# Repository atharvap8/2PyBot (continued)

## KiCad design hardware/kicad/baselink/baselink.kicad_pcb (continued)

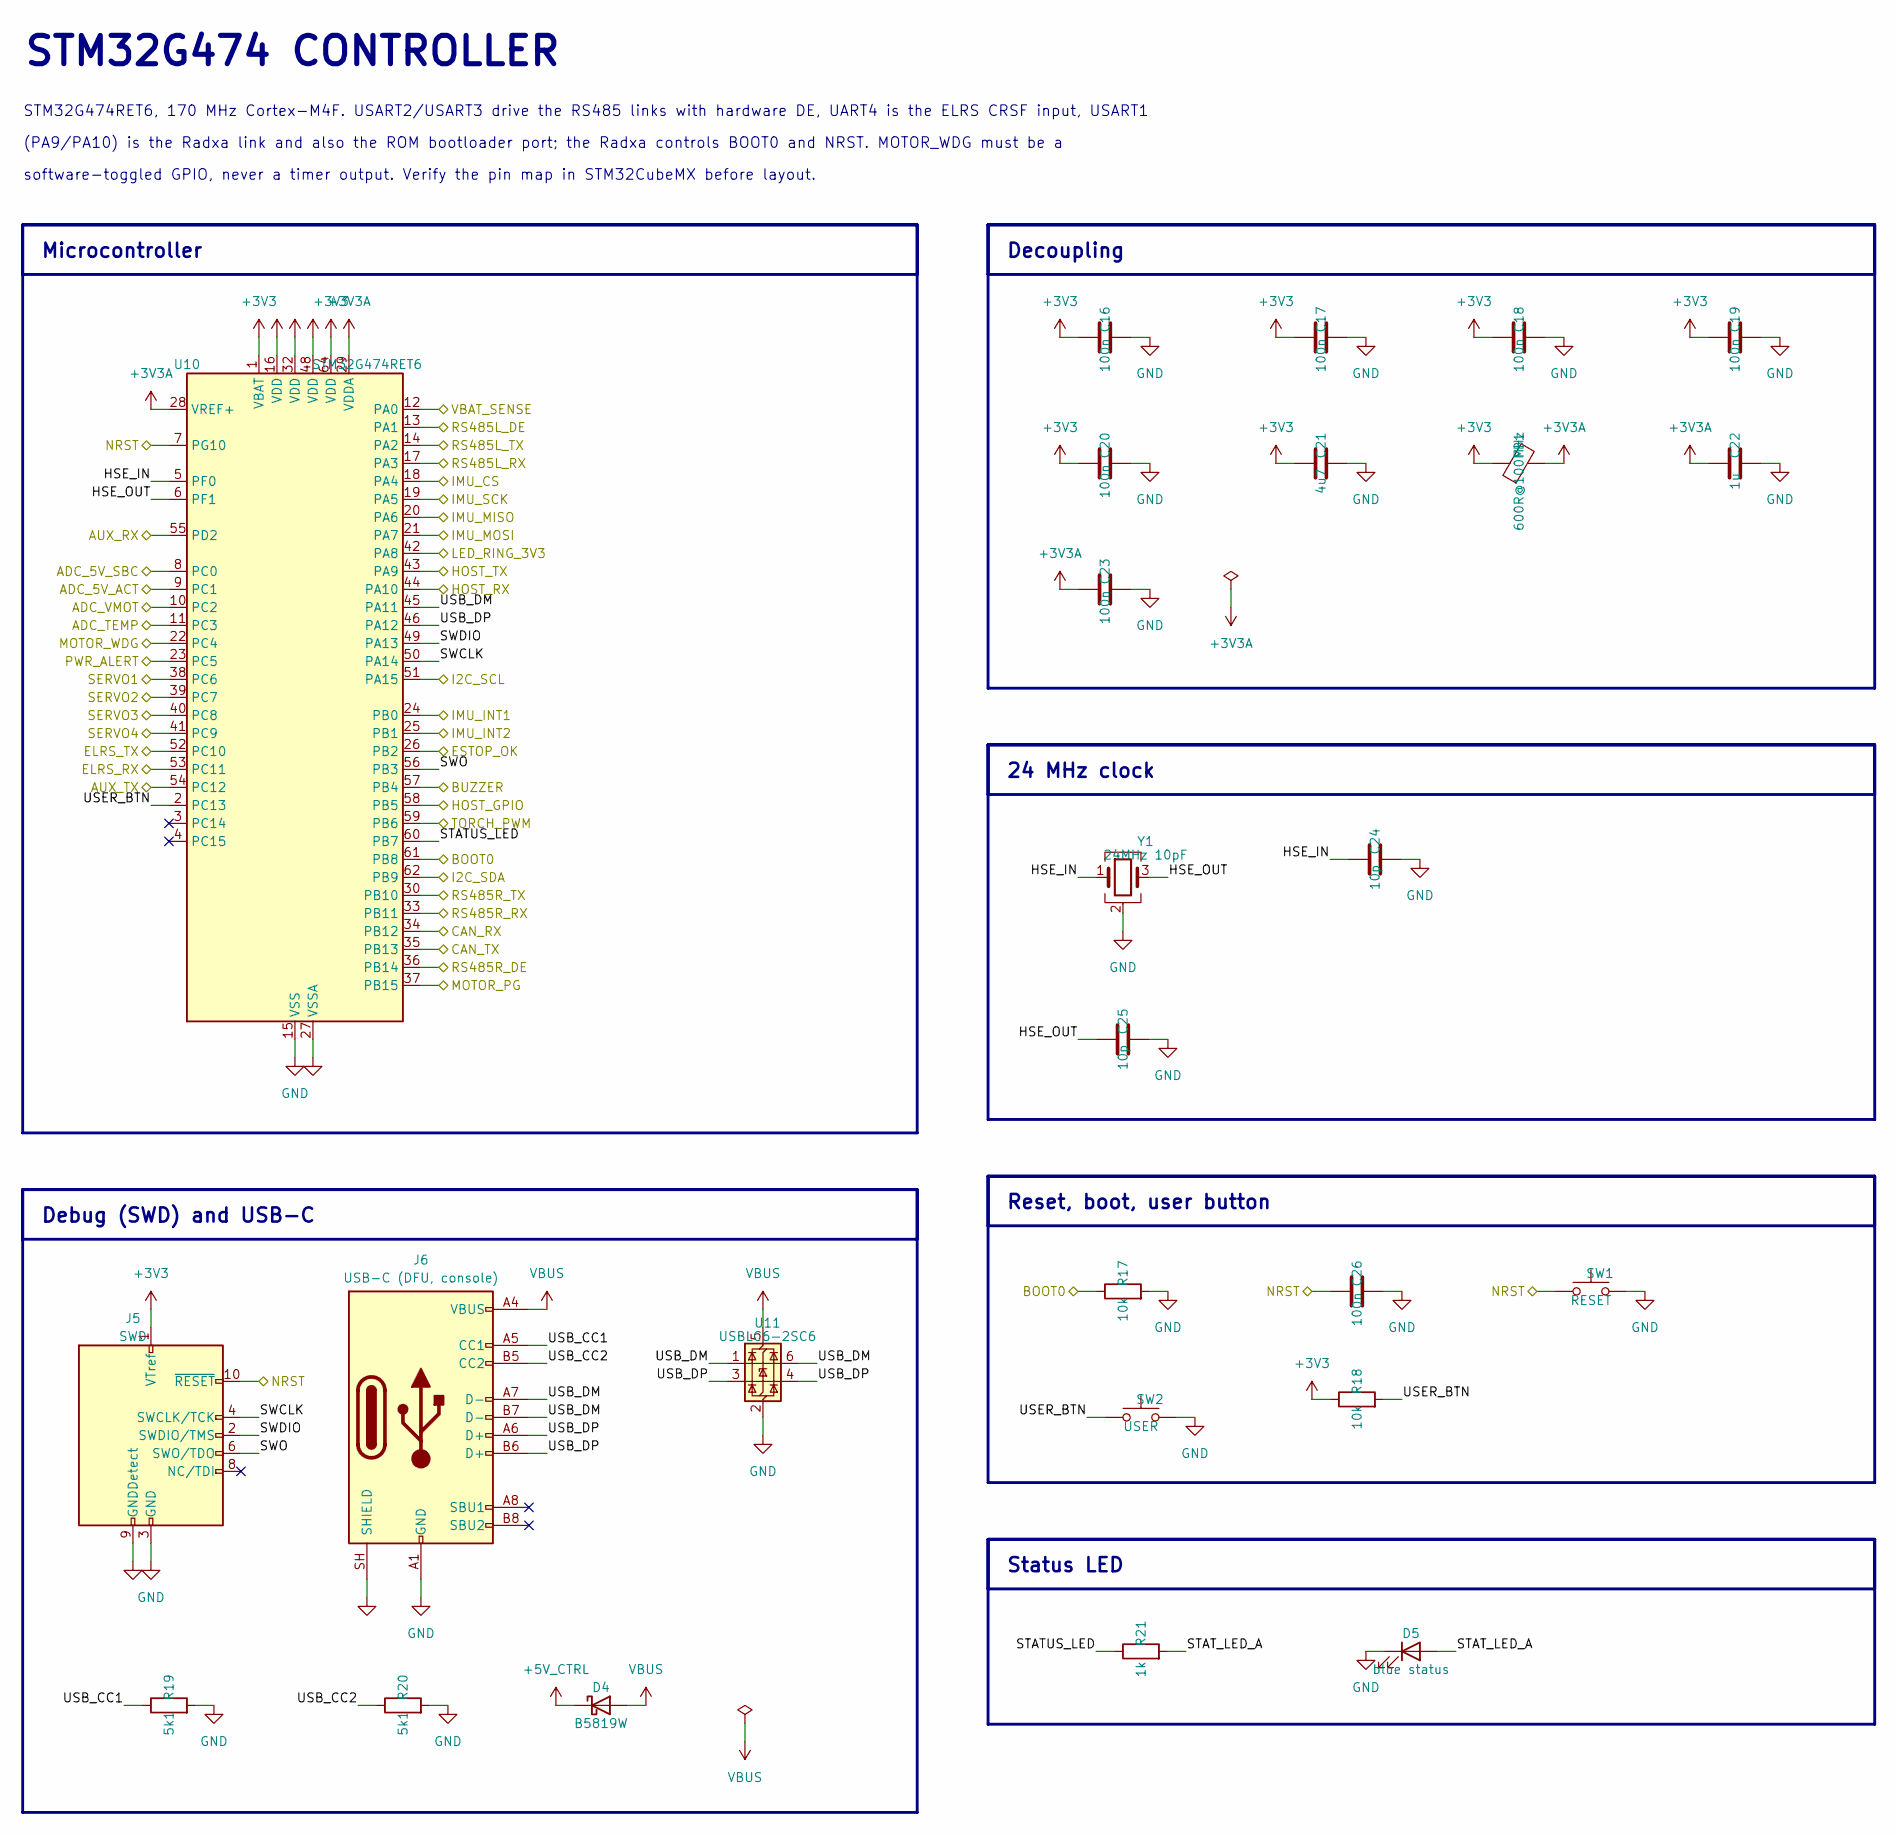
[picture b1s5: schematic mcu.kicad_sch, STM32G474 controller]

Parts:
C16, C17, C18, C19, C20, C23, C26: 100n; C_0603_1608Metric
C21: 4u7; C_0805_2012Metric
C22: 1u; C_0603_1608Metric
C24, C25: 10p; C_0603_1608Metric
D4: B5819W; D_SOD-123
D5: blue status; LED_0603_1608Metric
FB1: 600R@100MHz; L_0603_1608Metric
J5: SWD; PinHeader_2x05_P1.27mm_Vertical_SMD
J6: USB-C (DFU, console); USB_C_Receptacle_GCT_USB4105-xx-A_16P_TopMnt_Horizontal
R17, R18: 10k; R_0603_1608Metric
R19, R20: 5k1; R_0603_1608Metric
R21: 1k; R_0603_1608Metric
SW1: RESET; SW_SPST_TL3342
SW2: USER; SW_SPST_TL3342
U10: STM32G474RET6; LQFP-64_10x10mm_P0.5mm
U11: USBLC6-2SC6; SOT-23-6
Y1: 24MHz 10pF; Crystal_SMD_3225-4Pin_3.2x2.5mm

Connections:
+3V3: C16.1, C17.1, C18.1, C19.1, C20.1, C21.1, FB1.1, J5.1 (VTref), R18.1, U10.1 (VBAT), U10.16 (VDD), U10.32 (VDD), U10.48 (VDD), U10.64 (VDD); also elsewhere on the board
+3V3A: C22.1, C23.1, FB1.2, U10.28 (VREF+), U10.29 (VDDA)
+5V_CTRL: D4.1 (K); also elsewhere on the board
/ADC_5V_ACT: U10.9 (PC1); also elsewhere on the board
/ADC_5V_SBC: U10.8 (PC0); also elsewhere on the board
/ADC_TEMP: U10.11 (PC3); also elsewhere on the board
/ADC_VMOT: U10.10 (PC2); also elsewhere on the board
/AUX_RX: U10.55 (PD2); also elsewhere on the board
/AUX_TX: U10.54 (PC12); also elsewhere on the board
/BOOT0: R17.1, U10.61 (PB8); also elsewhere on the board
/BUZZER: U10.57 (PB4); also elsewhere on the board
/CAN_RX: U10.34 (PB12); also elsewhere on the board
/CAN_TX: U10.35 (PB13); also elsewhere on the board
/ELRS_RX: U10.53 (PC11); also elsewhere on the board
/ELRS_TX: U10.52 (PC10); also elsewhere on the board
/ESTOP_OK: U10.26 (PB2); also elsewhere on the board
/HOST_GPIO: U10.58 (PB5); also elsewhere on the board
/HOST_RX: U10.44 (PA10); also elsewhere on the board
/HOST_TX: U10.43 (PA9); also elsewhere on the board
/I2C_SCL: U10.51 (PA15); also elsewhere on the board
/I2C_SDA: U10.62 (PB9); also elsewhere on the board
/IMU_CS: U10.18 (PA4); also elsewhere on the board
/IMU_INT1: U10.24 (PB0); also elsewhere on the board
/IMU_INT2: U10.25 (PB1); also elsewhere on the board
/IMU_MISO: U10.20 (PA6); also elsewhere on the board
/IMU_MOSI: U10.21 (PA7); also elsewhere on the board
/IMU_SCK: U10.19 (PA5); also elsewhere on the board
/LED_RING_3V3: U10.42 (PA8); also elsewhere on the board
/MCU/HSE_IN: C24.1, U10.5 (PF0), Y1.1
/MCU/HSE_OUT: C25.1, U10.6 (PF1), Y1.3
/MCU/STATUS_LED: R21.1, U10.60 (PB7)
/MCU/STAT_LED_A: D5.2 (A), R21.2
/MCU/SWCLK: J5.4 (SWCLK/TCK), U10.50 (PA14)
/MCU/SWDIO: J5.2 (SWDIO/TMS), U10.49 (PA13)
/MCU/SWO: J5.6 (SWO/TDO), U10.56 (PB3)
/MCU/USB_CC1: J6.A5 (CC1), R19.1
/MCU/USB_CC2: J6.B5 (CC2), R20.1
/MCU/USB_DM: J6.A7 (D-), J6.B7 (D-), U10.45 (PA11), U11.1 (I/O1), U11.6 (I/O1)
/MCU/USB_DP: J6.A6 (D+), J6.B6 (D+), U10.46 (PA12), U11.3 (I/O2), U11.4 (I/O2)
/MCU/USER_BTN: R18.2, SW2.1, U10.2 (PC13)
/MOTOR_PG: U10.37 (PB15); also elsewhere on the board
/MOTOR_WDG: U10.22 (PC4); also elsewhere on the board
/NRST: C26.1, J5.10 (~RESET), SW1.1, U10.7 (PG10); also elsewhere on the board
/PWR_ALERT: U10.23 (PC5); also elsewhere on the board
/RS485L_DE: U10.13 (PA1); also elsewhere on the board
/RS485L_RX: U10.17 (PA3); also elsewhere on the board
/RS485L_TX: U10.14 (PA2); also elsewhere on the board
/RS485R_DE: U10.36 (PB14); also elsewhere on the board
/RS485R_RX: U10.33 (PB11); also elsewhere on the board
/RS485R_TX: U10.30 (PB10); also elsewhere on the board
/SERVO1: U10.38 (PC6); also elsewhere on the board
/SERVO2: U10.39 (PC7); also elsewhere on the board
/SERVO3: U10.40 (PC8); also elsewhere on the board
/SERVO4: U10.41 (PC9); also elsewhere on the board
/TORCH_PWM: U10.59 (PB6); also elsewhere on the board
/VBAT_SENSE: U10.12 (PA0); also elsewhere on the board
GND: C16.2, C17.2, C18.2, C19.2, C20.2, C21.2, C22.2, C23.2, C24.2, C25.2, C26.2, D5.1 (K), J5.3 (GND), J5.5 (GND), J5.9 (GNDDetect), J6.A1 (GND), J6.A12 (GND), J6.B1 (GND), J6.B12 (GND), J6.SH (SHIELD), R17.2, R19.2, R20.2, SW1.2, SW2.2, U10.15 (VSS), U10.27 (VSSA), U10.31 (VSS), U10.47 (VSS), U10.63 (VSS), U11.2 (GND), Y1.2 (G), Y1.4 (G); also elsewhere on the board
VBUS: D4.2 (A), J6.A4 (VBUS), J6.A9 (VBUS), J6.B4 (VBUS), J6.B9 (VBUS), U11.5 (VBUS)

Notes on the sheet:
STM32G474 CONTROLLER
STM32G474RET6, 170 MHz Cortex-M4F. USART2/USART3 drive the RS485 links with hardware DE, UART4 is the ELRS CRSF input, USART1
(PA9/PA10) is the Radxa link and also the ROM bootloader port; the Radxa controls BOOT0 and NRST. MOTOR_WDG must be a
software-toggled GPIO, never a timer output. Verify the pin map in STM32CubeMX before layout.
Microcontroller
Decoupling
24 MHz clock
Reset, boot, user button
Debug (SWD) and USB-C
Status LED

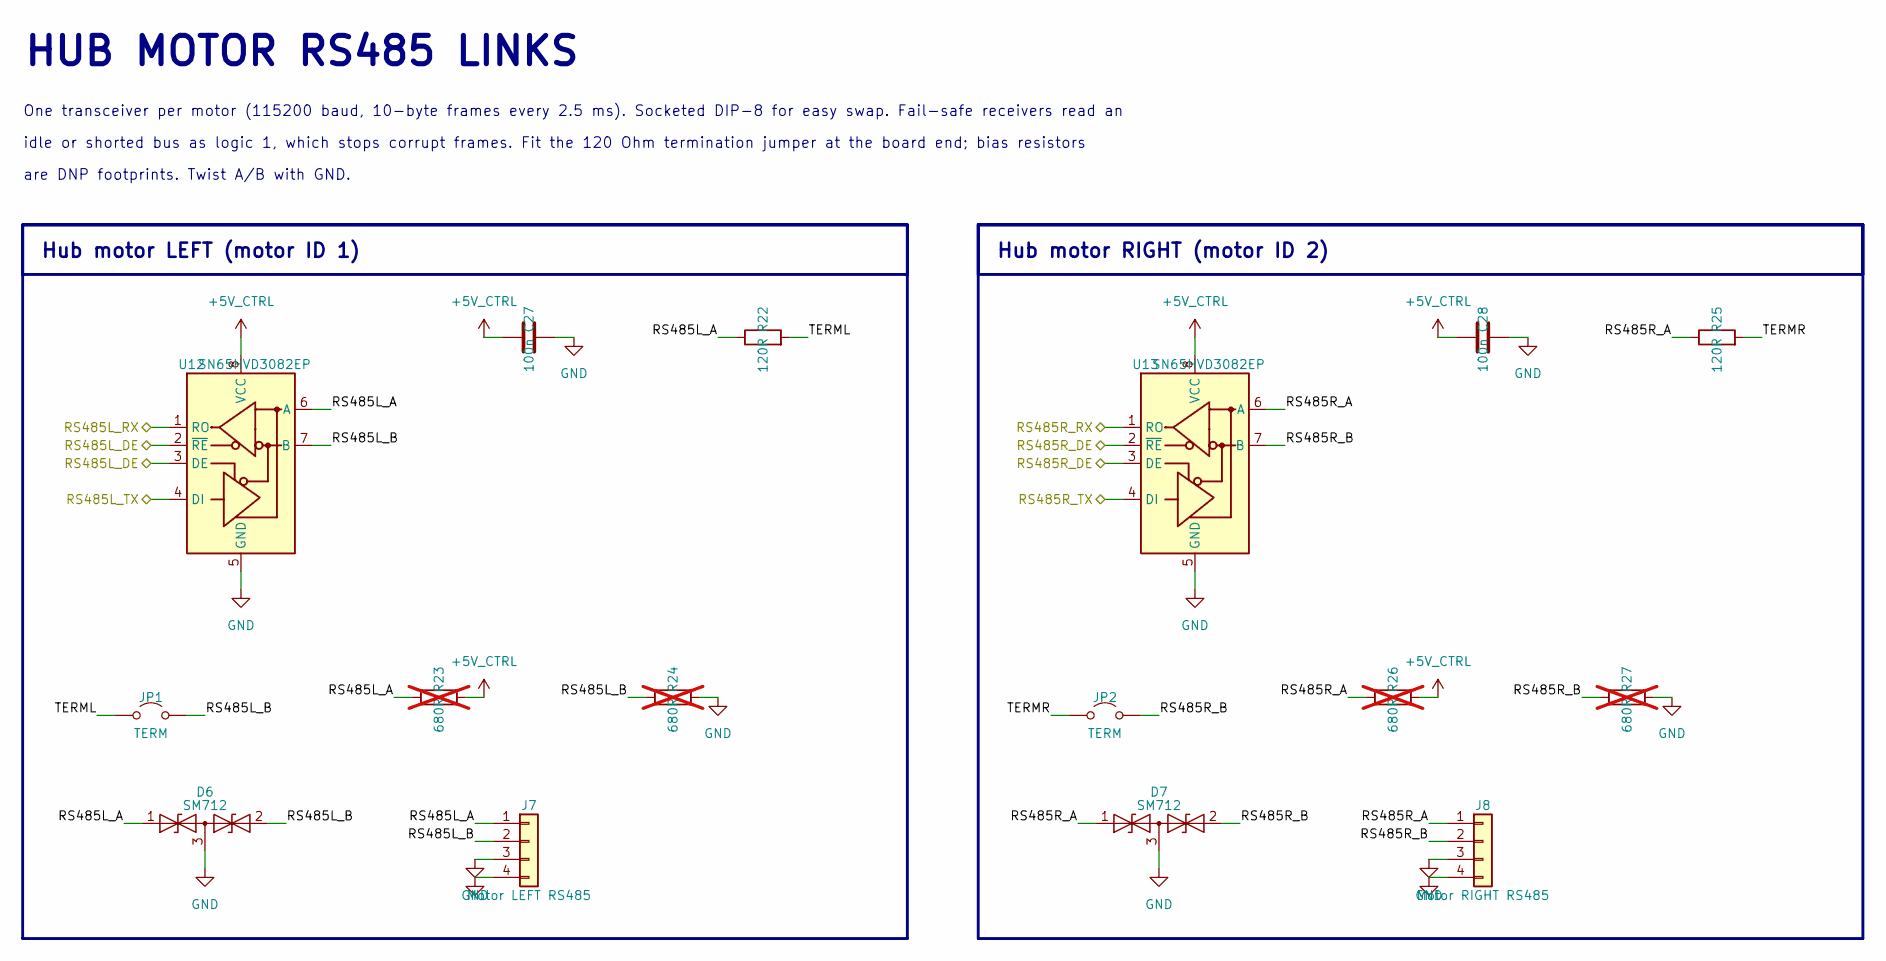
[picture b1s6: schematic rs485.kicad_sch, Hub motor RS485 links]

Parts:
C27, C28: 100n; C_0603_1608Metric
D6, D7: SM712; SOT-23
J7: Motor LEFT RS485; JST_GH_SM04B-GHS-TB_1x04-1MP_P1.25mm_Horizontal
J8: Motor RIGHT RS485; JST_GH_SM04B-GHS-TB_1x04-1MP_P1.25mm_Horizontal
JP1, JP2: TERM; PinHeader_1x02_P2.54mm_Vertical
R22, R25: 120R; R_0603_1608Metric
R23, R24, R26, R27: 680R; R_0603_1608Metric; not fitted
U12, U13: SN65HVD3082EP; DIP-8_W7.62mm_Socket

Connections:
+5V_CTRL: C27.1, C28.1, R23.2, R26.2, U12.8 (VCC), U13.8 (VCC); also elsewhere on the board
/RS485/RS485L_A: D6.1 (A1), J7.1, R22.1, R23.1, U12.6 (A)
/RS485/RS485L_B: D6.2 (A2), J7.2, JP1.2 (B), R24.1, U12.7 (B)
/RS485/RS485R_A: D7.1 (A1), J8.1, R25.1, R26.1, U13.6 (A)
/RS485/RS485R_B: D7.2 (A2), J8.2, JP2.2 (B), R27.1, U13.7 (B)
/RS485/TERML: JP1.1 (A), R22.2
/RS485/TERMR: JP2.1 (A), R25.2
/RS485L_DE: U12.2 (~RE), U12.3 (DE); also elsewhere on the board
/RS485L_RX: U12.1 (RO); also elsewhere on the board
/RS485L_TX: U12.4 (DI); also elsewhere on the board
/RS485R_DE: U13.2 (~RE), U13.3 (DE); also elsewhere on the board
/RS485R_RX: U13.1 (RO); also elsewhere on the board
/RS485R_TX: U13.4 (DI); also elsewhere on the board
GND: C27.2, C28.2, D6.3 (common), D7.3 (common), J7.3, J7.4, J8.3, J8.4, R24.2, R27.2, U12.5 (GND), U13.5 (GND); also elsewhere on the board

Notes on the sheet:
HUB MOTOR RS485 LINKS
One transceiver per motor (115200 baud, 10-byte frames every 2.5 ms). Socketed DIP-8 for easy swap. Fail-safe receivers read an
idle or shorted bus as logic 1, which stops corrupt frames. Fit the 120 Ohm termination jumper at the board end; bias resistors
are DNP footprints. Twist A/B with GND.
Hub motor LEFT (motor ID 1)
Hub motor RIGHT (motor ID 2)

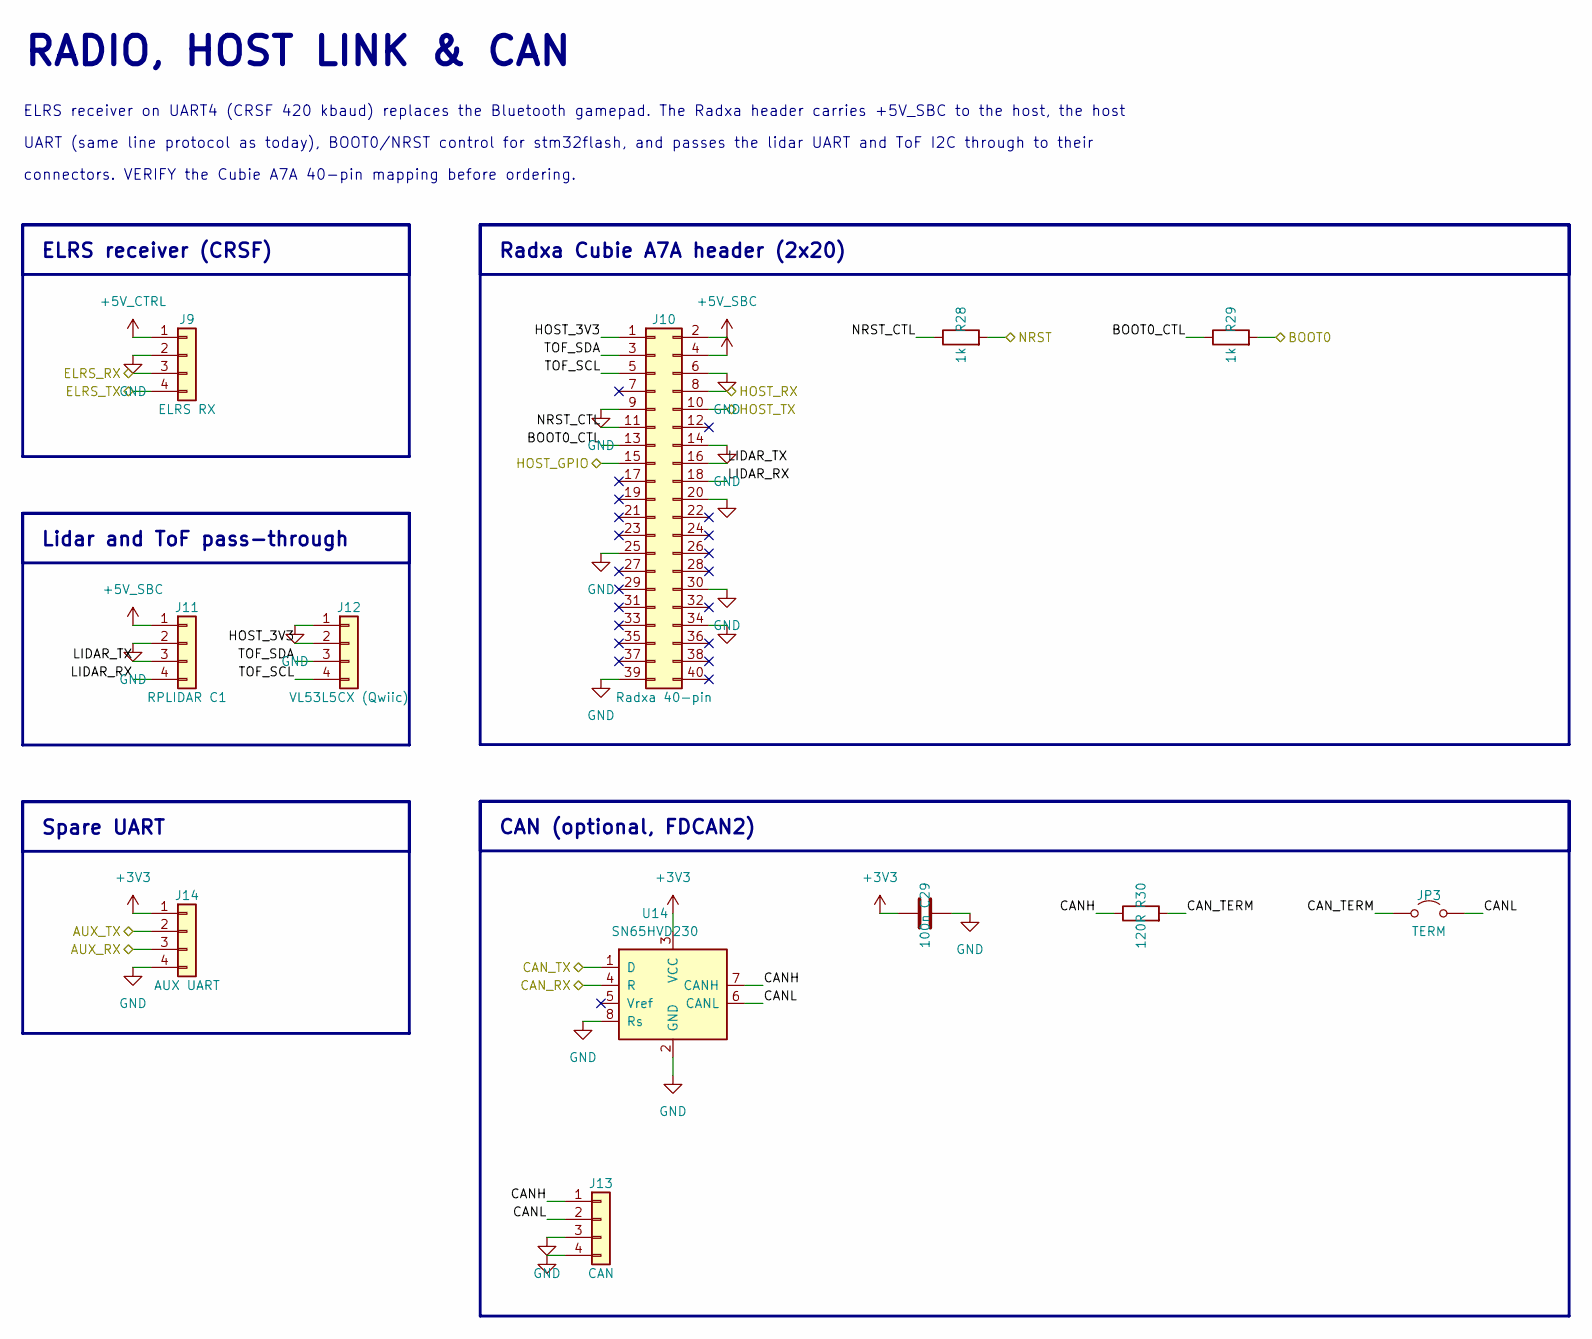
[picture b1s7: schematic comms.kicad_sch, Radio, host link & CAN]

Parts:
C29: 100n; C_0603_1608Metric
J9: ELRS RX; JST_GH_SM04B-GHS-TB_1x04-1MP_P1.25mm_Horizontal
J10: Radxa 40-pin; PinSocket_2x20_P2.54mm_Vertical
J11: RPLIDAR C1; JST_GH_SM04B-GHS-TB_1x04-1MP_P1.25mm_Horizontal
J12: VL53L5CX (Qwiic); JST_SH_SM04B-SRSS-TB_1x04-1MP_P1.00mm_Horizontal
J13: CAN; JST_GH_SM04B-GHS-TB_1x04-1MP_P1.25mm_Horizontal
J14: AUX UART; JST_GH_SM04B-GHS-TB_1x04-1MP_P1.25mm_Horizontal
JP3: TERM; PinHeader_1x02_P2.54mm_Vertical
R28, R29: 1k; R_0603_1608Metric
R30: 120R; R_0603_1608Metric
U14: SN65HVD230; SOIC-8_3.9x4.9mm_P1.27mm

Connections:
+3V3: C29.1, J14.1, U14.3 (VCC); also elsewhere on the board
+5V_CTRL: J9.1; also elsewhere on the board
+5V_SBC: J10.2, J10.4, J11.1; also elsewhere on the board
/AUX_RX: J14.3; also elsewhere on the board
/AUX_TX: J14.2; also elsewhere on the board
/BOOT0: R29.2; also elsewhere on the board
/CAN_RX: U14.4 (R); also elsewhere on the board
/CAN_TX: U14.1 (D); also elsewhere on the board
/Comms/BOOT0_CTL: J10.13, R29.1
/Comms/CANH: J13.1, R30.1, U14.7 (CANH)
/Comms/CANL: J13.2, JP3.2 (B), U14.6 (CANL)
/Comms/CAN_TERM: JP3.1 (A), R30.2
/Comms/HOST_3V3: J10.1, J12.2
/Comms/LIDAR_RX: J10.18, J11.4
/Comms/LIDAR_TX: J10.16, J11.3
/Comms/NRST_CTL: J10.11, R28.1
/Comms/TOF_SCL: J10.5, J12.4
/Comms/TOF_SDA: J10.3, J12.3
/ELRS_RX: J9.3; also elsewhere on the board
/ELRS_TX: J9.4; also elsewhere on the board
/HOST_GPIO: J10.15; also elsewhere on the board
/HOST_RX: J10.8; also elsewhere on the board
/HOST_TX: J10.10; also elsewhere on the board
/NRST: R28.2; also elsewhere on the board
GND: C29.2, J9.2, J10.6, J10.9, J10.14, J10.20, J10.25, J10.30, J10.34, J10.39, J11.2, J12.1, J13.3, J13.4, J14.4, U14.2 (GND), U14.8 (Rs); also elsewhere on the board

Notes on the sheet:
RADIO, HOST LINK & CAN
ELRS receiver on UART4 (CRSF 420 kbaud) replaces the Bluetooth gamepad. The Radxa header carries +5V_SBC to the host, the host
UART (same line protocol as today), BOOT0/NRST control for stm32flash, and passes the lidar UART and ToF I2C through to their
connectors. VERIFY the Cubie A7A 40-pin mapping before ordering.
ELRS receiver (CRSF)
Radxa Cubie A7A header (2x20)
Lidar and ToF pass-through
CAN (optional, FDCAN2)
Spare UART

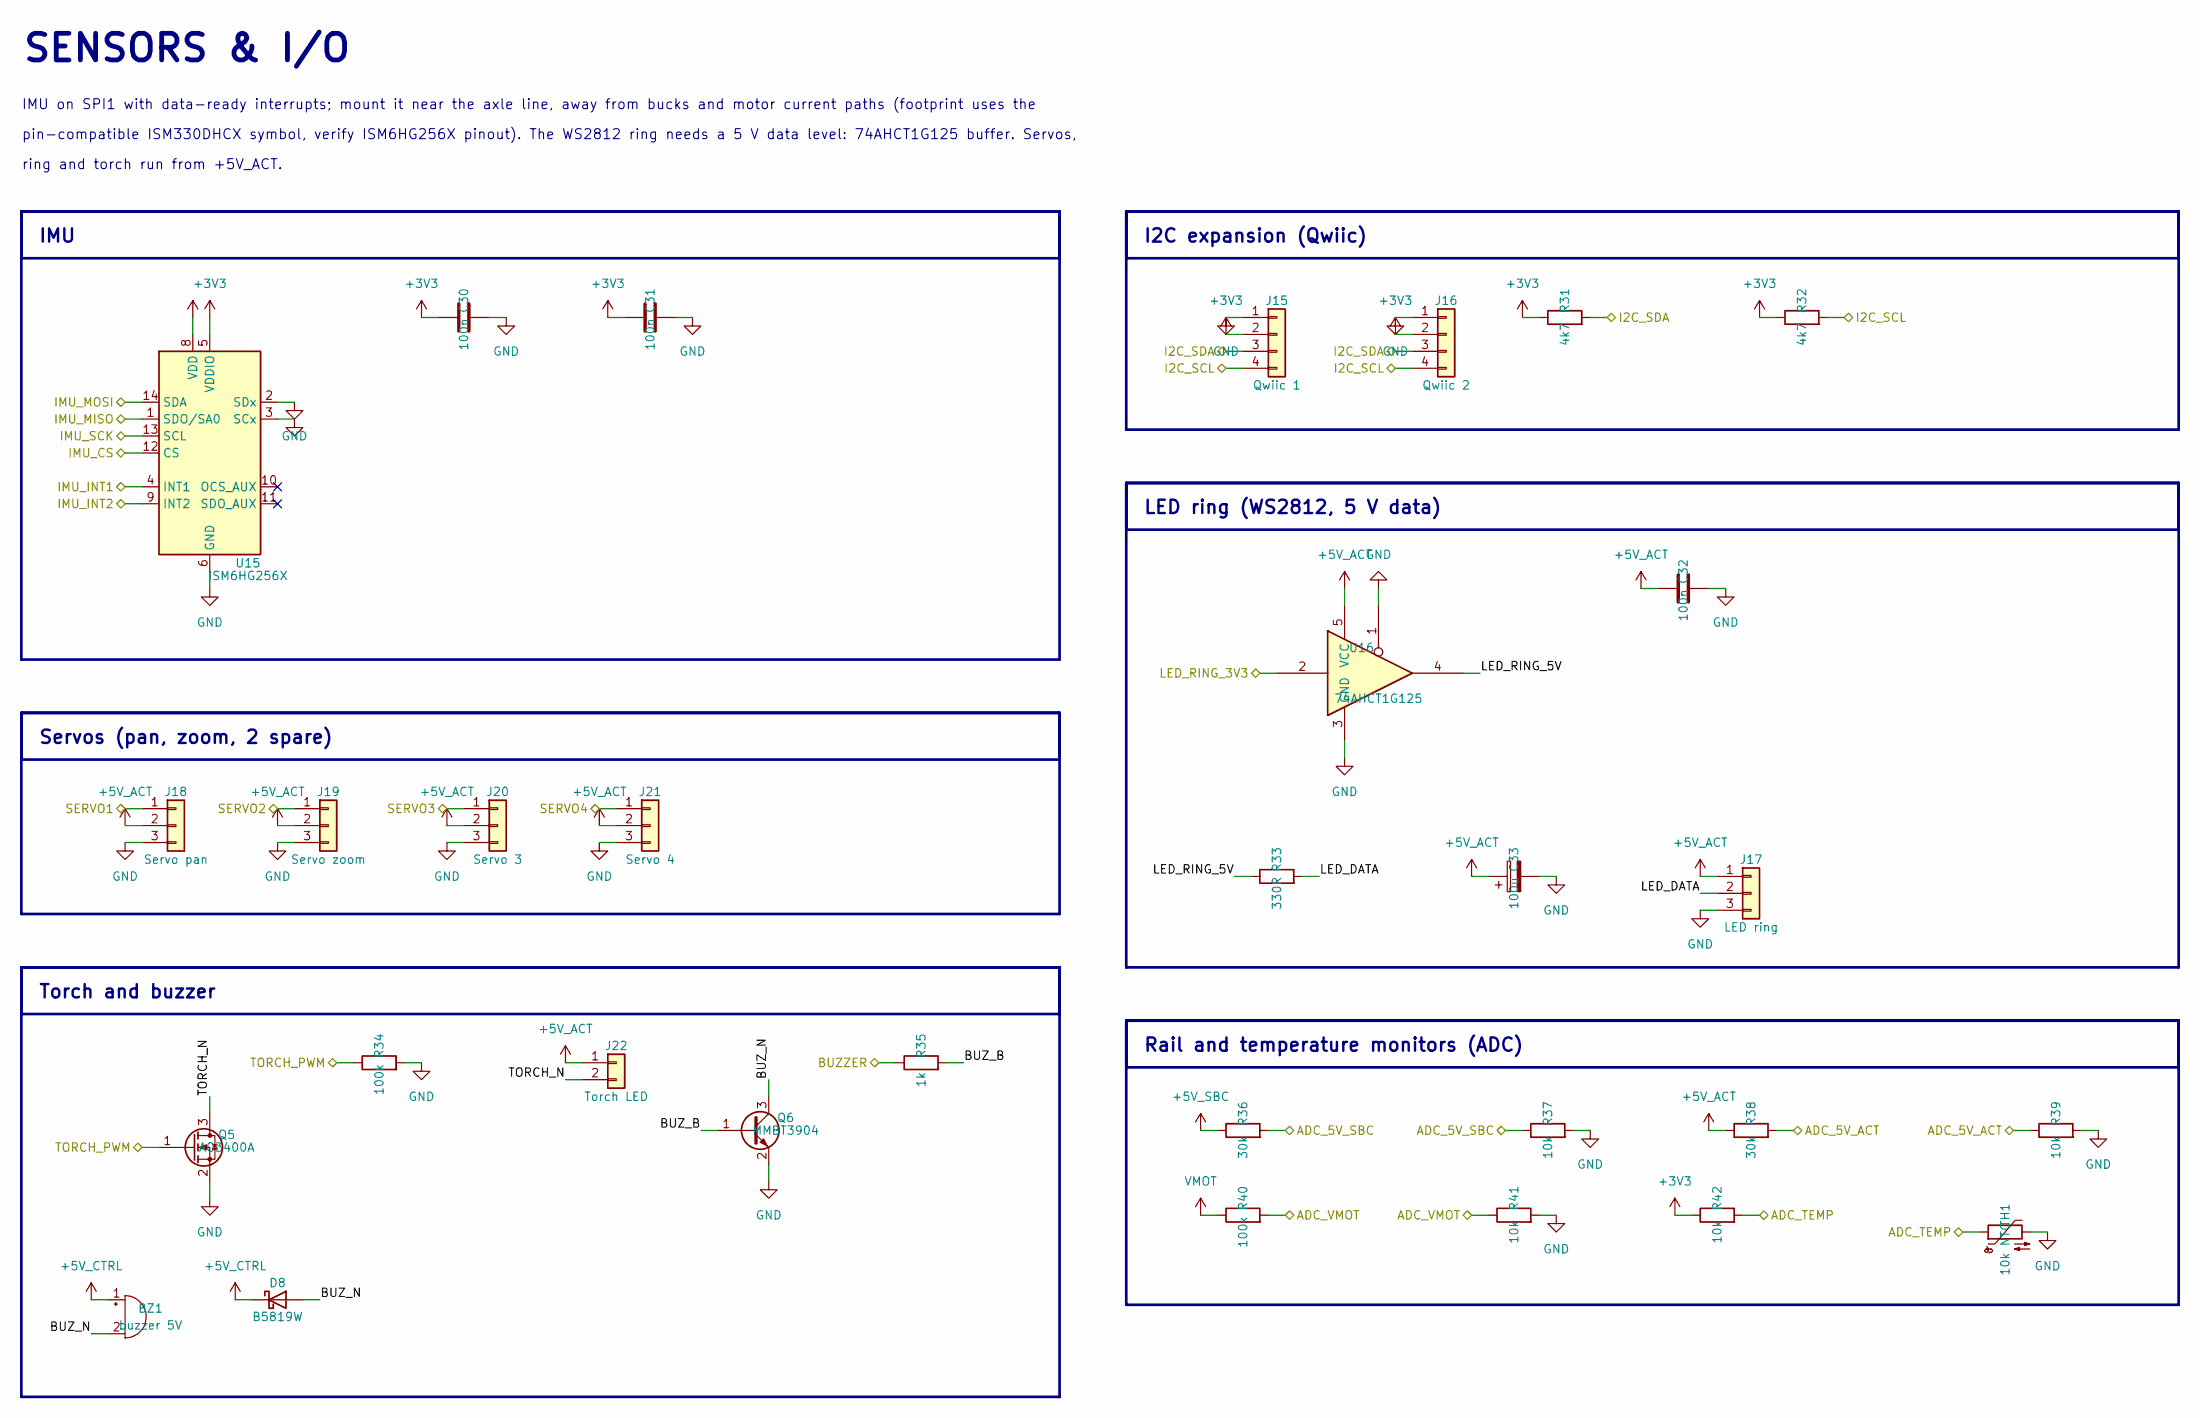
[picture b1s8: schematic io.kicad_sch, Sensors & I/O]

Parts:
BZ1: buzzer 5V; Buzzer_12x9.5RM7.6
C30, C31, C32: 100n; C_0603_1608Metric
C33: 100u; CP_Elec_6.3x7.7
D8: B5819W; D_SOD-123
J15: Qwiic 1; JST_SH_SM04B-SRSS-TB_1x04-1MP_P1.00mm_Horizontal
J16: Qwiic 2; JST_SH_SM04B-SRSS-TB_1x04-1MP_P1.00mm_Horizontal
J17: LED ring; JST_PH_S3B-PH-K_1x03_P2.00mm_Horizontal
J18: Servo pan; PinHeader_1x03_P2.54mm_Vertical
J19: Servo zoom; PinHeader_1x03_P2.54mm_Vertical
J20: Servo 3; PinHeader_1x03_P2.54mm_Vertical
J21: Servo 4; PinHeader_1x03_P2.54mm_Vertical
J22: Torch LED; PinHeader_1x02_P2.54mm_Vertical
Q5: AO3400A; SOT-23
Q6: MMBT3904; SOT-23
R31, R32: 4k7; R_0603_1608Metric
R33: 330R; R_0603_1608Metric
R34, R40: 100k; R_0603_1608Metric
R35: 1k; R_0603_1608Metric
R36, R38: 30k; R_0603_1608Metric
R37, R39, R41, R42: 10k; R_0603_1608Metric
TH1: 10k NTC; R_0603_1608Metric
U15: ISM6HG256X; LGA-14_3x2.5mm_P0.5mm_LayoutBorder3x4y
U16: 74AHCT1G125; SOT-23-5

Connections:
+3V3: C30.1, C31.1, J15.2, J16.2, R31.1, R32.1, R42.1, U15.5 (VDDIO), U15.8 (VDD); also elsewhere on the board
+5V_ACT: C32.1, C33.1, J17.1, J18.2, J19.2, J20.2, J21.2, J22.1, R38.1, U16.5 (VCC); also elsewhere on the board
+5V_CTRL: BZ1.1 (+), D8.1 (K); also elsewhere on the board
+5V_SBC: R36.1; also elsewhere on the board
/ADC_5V_ACT: R38.2, R39.1; also elsewhere on the board
/ADC_5V_SBC: R36.2, R37.1; also elsewhere on the board
/ADC_TEMP: R42.2, TH1.1; also elsewhere on the board
/ADC_VMOT: R40.2, R41.1; also elsewhere on the board
/BUZZER: R35.1; also elsewhere on the board
/I2C_SCL: J15.4, J16.4, R32.2; also elsewhere on the board
/I2C_SDA: J15.3, J16.3, R31.2; also elsewhere on the board
/IMU_CS: U15.12 (CS); also elsewhere on the board
/IMU_INT1: U15.4 (INT1); also elsewhere on the board
/IMU_INT2: U15.9 (INT2); also elsewhere on the board
/IMU_MISO: U15.1 (SDO/SA0); also elsewhere on the board
/IMU_MOSI: U15.14 (SDA); also elsewhere on the board
/IMU_SCK: U15.13 (SCL); also elsewhere on the board
/IO/BUZ_B: Q6.1 (B), R35.2
/IO/BUZ_N: BZ1.2 (-), D8.2 (A), Q6.3 (C)
/IO/LED_DATA: J17.2, R33.2
/IO/LED_RING_5V: R33.1, U16.4
/IO/TORCH_N: J22.2, Q5.3 (D)
/LED_RING_3V3: U16.2; also elsewhere on the board
/SERVO1: J18.1; also elsewhere on the board
/SERVO2: J19.1; also elsewhere on the board
/SERVO3: J20.1; also elsewhere on the board
/SERVO4: J21.1; also elsewhere on the board
/TORCH_PWM: Q5.1 (G), R34.1; also elsewhere on the board
GND: C30.2, C31.2, C32.2, C33.2, J15.1, J16.1, J17.3, J18.3, J19.3, J20.3, J21.3, Q5.2 (S), Q6.2 (E), R34.2, R37.2, R39.2, R41.2, TH1.2, U15.2 (SDx), U15.3 (SCx), U15.6 (GND), U15.7 (GND), U16.1, U16.3 (GND); also elsewhere on the board
VMOT: R40.1; also elsewhere on the board

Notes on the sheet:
SENSORS & I/O
IMU on SPI1 with data-ready interrupts; mount it near the axle line, away from bucks and motor current paths (footprint uses the
pin-compatible ISM330DHCX symbol, verify ISM6HG256X pinout). The WS2812 ring needs a 5 V data level: 74AHCT1G125 buffer. Servos,
ring and torch run from +5V_ACT.
IMU
I2C expansion (Qwiic)
LED ring (WS2812, 5 V data)
Servos (pan, zoom, 2 spare)
Torch and buzzer
Rail and temperature monitors (ADC)

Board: 4 copper layers, 144 parts (0 on the bottom side), 102 nets, no tracks yet.

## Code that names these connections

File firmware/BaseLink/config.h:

/* 2PyBot v5.5.0: ESP32 + M0601 BLDC hubs.
 * Control state is robot-forward SI; the wire layer applies motor polarity.
 * Pinout and geometry follow the supplied BaseLinkHub program.
 */
#ifndef CONFIG_H
#define CONFIG_H

#define RIGHT_MOTOR_ID       2
#define RIGHT_RS485_TX       19
#define RIGHT_RS485_RX       18
#define RIGHT_RS485_DE       23
#define LEFT_MOTOR_ID        1
#define LEFT_RS485_TX        17
#define LEFT_RS485_RX        16
#define LEFT_RS485_DE        4
#define RIGHT_MOTOR_DIR      (+1.0f)
#define LEFT_MOTOR_DIR       (-1.0f)
// Confirmed by the owner. Not inherited from either old NVS namespace.
#define HUB_CURRENT_SIGN    (-1.0f)
#define HUB_RPM_SIGN        (-1.0f)

#define I2C_SDA             21
#define I2C_SCL             22
#define I2C_CLOCK_HZ        400000
#define SUPPLY_V            18.0f // owner-confirmed 5S Li-ion operating supply; estimate, not a voltage sensor
#define M0601_KT            0.75f
#define M0601_KV_RPM_PER_V   11.1f
#define M0601_CPR           4096
#define ENCODER_CPR         M0601_CPR
#define MOTOR_CURRENT_MA    2700
#define MOTOR_CURRENT_MAX_MA 4400
#define HUB_DRIVE_MODE      1 // current/torque control only
#define HUB_LINK_TIMEOUT_MS 60

// Lower sampled velocity-loop gains reduce the current reversals observed
// under load with delayed position feedback. Full torque remains available.
#define HUB_KP              4.0f
#define HUB_KI              4.0f
#define HUB_INT_LIM         0.5f
#define HUB_KFF             1.0f
#define HUB_MASS_KG         2.6f
#define HUB_VEL_SOURCE      1 // owner-confirmed fix: position-derived velocity
#define HUB_YAW_KP          1.5f
#define HUB_YAW_KI          2.0f
#define HUB_YAW_INT_LIM     0.35f
#define HUB_YAW_CURRENT_SLEW 0.0f // direct differential-current response

#define WHEEL_RADIUS_M      0.0520f
#define COUNTS_PER_M        ((float)ENCODER_CPR / (2.0f * PI * WHEEL_RADIUS_M))
#define STEPS_PER_M         COUNTS_PER_M // retained protocol name; counts, not microsteps
#define TRACK_WIDTH_M       0.155f
#define PITCH_FWD_SIGN      (-1.0f)
#define ENC_FWD_SIGN        (+1.0f)
#define RATE_FWD_SIGN       (+1.0f)
#define PITCH_TRIM_DEG      -1.2603f // fixed owner-requested raw neutral IMU angle

// Keep the supplied LQI design; the actuator loop and speed windup are
// corrected separately rather than guessing new body gains without a log.
#define LQR_K1              (-7.3234f)
#define LQR_K2              (-7.4495f)
#define LQR_K3              (-42.9506f)
#define LQR_K4              (-6.6862f)
#define LQR_K5              (-2.1082f)
#define Z_INT_LIM           0.5f
#define EX_CLAMP_M          0.15f
#define VSAT_BLEED          3.0f
#define V_HOLD_MAX_MS       0.35f
#define BRAKE_LOOKAHEAD_S    0.30f
#define LQR_S1              (-60.0226f)
#define LQR_S2              (-31.0364f)
#define LQR_S3              (-82.0431f)
#define LQR_S4              (-10.2571f)
#define LQR_S5              (-25.8199f)
#define LQR_C1              (-22.2369f)
#define LQR_C2              (-20.0745f)
#define LQR_C3              (-81.3063f)
#define LQR_C4              (-12.7029f)
#define LQR_C5              (-8.1650f)
#define CLIMB_Z_INT_LIM     2.0f
#define CLIMB_VEL_MS        0.25f
#define CLIMB_STEER_SCALE   0.40f
#define LOOK_MAX_DEG        18.0f

// MAXSPD=0 is uncapped. The voltage/free-speed model is telemetry only.
#define MAX_SPEED_STEPS     0.0f
#define MOTOR_ACCEL_LIMIT   (6.0f * COUNTS_PER_M)
#define MAX_DRIVE_VEL_MS     1.00f   // operator reference; no voltage/free-speed derating
// Legacy saved setting only; no longer used to clamp drive requests.
#define SPEED_HEADROOM       0.70f
#define DRIVE_DEADBAND      0.03f
#define JOY_FWD_SCALE       (-0.2f)
#define JOY_STEER_SCALE     1.0f
#define MAX_STEER_STEPS     4000.0f // fixed owner-requested differential encoder counts/s
#define STEER_SLEW          0.0f // no commanded-turn slew
#define STEER_DEADBAND      0.05f
#define YAW_HOLD_KP         1.5f
#define YAW_HOLD_KD         0.03f
#define YAW_HOLD_MAX_STEPS  (0.8f * TRACK_WIDTH_M * COUNTS_PER_M * 0.5f)
#define YAW_RELATCH_COUNTS  2000.0f
#define YAW_TILT_SUSPEND_DEG 12.0f

#define RADXA_TIMEOUT_MS    600
#define JOY_TIMEOUT_MS_CFG  200
#define HOST_BOOT_WAIT      1.0f
#define ARM_ANGLE_DEG       5.0f
#define MAX_TILT_ANGLE      55.0f
#define MAX_PITCH_RATE_SAFETY 450.0f
#define STARTUP_SETTLE_MS   3000
#define IMU_FILTER_CUTOFF_HZ 50.0f
#define MAHONY_KP           2.0f
#define MAHONY_KI           0.005f
#define MAG_OFFSET_X        0.0f
#define MAG_OFFSET_Y        0.0f
#define MAG_OFFSET_Z        0.0f
#define MAG_SIGN_X          1
#define MAG_SIGN_Y          1
#define MAG_SIGN_Z          1
#define GYRO_CAL_SAMPLES    500
#define PITCH_ACCEL_PRIMARY 'Y'
#define PITCH_ACCEL_SECONDARY 'Z'
#define PITCH_ACCEL_SIGN    -1
#define PITCH_GYRO_AXIS     'X'
#define PITCH_GYRO_SIGN     -1
#define IMU_ODR_HZ          960.0f
#define IMU_ACCEL_FS        4
#define IMU_GYRO_FS         2000
#define LOOP_FREQ_HZ        200
#define LOOP_PERIOD_US      (1000000UL / LOOP_FREQ_HZ)
#define SERIAL_BAUD         460800
#define ODOM_PERIOD_MS      20
#define DEBUG_PERIOD_MS     20

#define LED_RING_PIN        15
#define LED_RING_COUNT      16
#define LED_FRONT_INDEX     9.0f   // owner-confirmed with LT,1 / LT,2 (ring re-mounted)
#define LED_DIR_CW          1
#define LED_MAX_BRIGHT      200
#define LED_FPS             50
// Blue power-button LED: GPIO32 -> LED+, LED- -> GND.
// Channel 0/timer 0 are separate from servo channels 4/5 and torch channel 6.
#define STATUS_LED_PIN      32
#define STATUS_LED_CH       0
#define STATUS_LED_ACTIVE_HIGH 1
#define STATUS_LED_PWM_HZ   1000
#define STATUS_LED_PWM_BITS 8
#define PAD_FWD_SIGN        (+1.0f)
#define PAD_STEER_SIGN      (-1.0f)
#define PAD_DEADZONE        0.08f
#define STICK_DEADZONE      0.10f
#define SNAP_IN_DEG         10.0f
#define SNAP_OUT_DEG        26.0f
#define EXPO_STEER          0.0f
#define EXPO_DRIVE          0.35f
#define STICK_AUTOCAL       1
#define SPEED_LO_DRIVE_SCALE 0.50f
#define SPEED_LO_STEER_SCALE 1.0f
#define SPEED_BOOT_HIGH     0

// Supplied BLDC harness: pan moved to 26; zoom is 0, torch remains 2.
#define SERVO_YAW_PIN       26
#define SERVO_ZOOM_PIN      0
#define TORCH_PIN           2
#define SERVO_YAW_CH        4
#define SERVO_ZOOM_CH       5
#define TORCH_CH            6
#define SERVO_PWM_HZ        50
#define SERVO_PWM_BITS      16
#define TORCH_PWM_HZ        20000
#define TORCH_PWM_BITS      10
#define SERVO_US_MIN        500.0f
#define SERVO_US_MAX        2400.0f
#define SERVO_YAW_MIN_DEG   120
#define SERVO_YAW_MAX_DEG   190
#define SERVO_YAW_HOME_DEG  165
#define SERVO_ZOOM_MIN_DEG  80
#define SERVO_ZOOM_MAX_DEG  140
#define SERVO_ZOOM_HOME_DEG 120
#define SERVO_YAW_RATE_DPS  70.0f
#define SERVO_ZOOM_RATE_DPS 45.0f
#define SERVO_UPDATE_HZ     50
#define SERVO_IDLE_RELEASE_MS 0
#define TORCH_MAX_PCT       90
#define TORCH_MIN_PCT       5
#define TORCH_BOOT_PCT      25
#define TORCH_STEP_PCT      10
#define TORCH_OFF_ON_DISARM 0
#define PAD_YAW_SIGN        (-1.0f)
#define PAD_ZOOM_SIGN       (+1.0f)
#define PAD_REPEAT_FIRST_MS 400
#define PAD_REPEAT_MS       130
#endif
